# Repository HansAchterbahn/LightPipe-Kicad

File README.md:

# LightPipe - Main PCB (Kicad)

LightPipes are colorful lighting pipes that can be combined to create complex and interesting geometries. The LightPipe project is based on the easily addressable APA102 RGB LEDs. Each LED in a LightPipe geometry can be addressed individually.

The LightPipe project uses the PCB in this project in a slightly modified form as input and output PCB. On the input side, it simply accepts data from a 3.5 jack and power from an XT30 connector. On the output side, the data is output to the next LightPipe via the same jack and power is supplied via the same XT30 connector.

An additional 3.5 female connector is used to tunnel the data from the output PCB back to the input PCB. With this arrangement it is possible to realize a complete tree structure and therefore to create arbitrary geometries.

In this repository you will find the schematics and board layouts created in KiCad. You will also find a 3D model of the PCB.

*Fork me and have fun!*

**LightPipe - First Prototyep @ Neotopia Hackspace in Göttingen**

## PCB 3D view

Animated 3D STL model: [kibot/3d/model](kibot/3d/model)

__Top view__

__Bottom view__

## Schematic

## Board

__Top view__

__Bottom view__

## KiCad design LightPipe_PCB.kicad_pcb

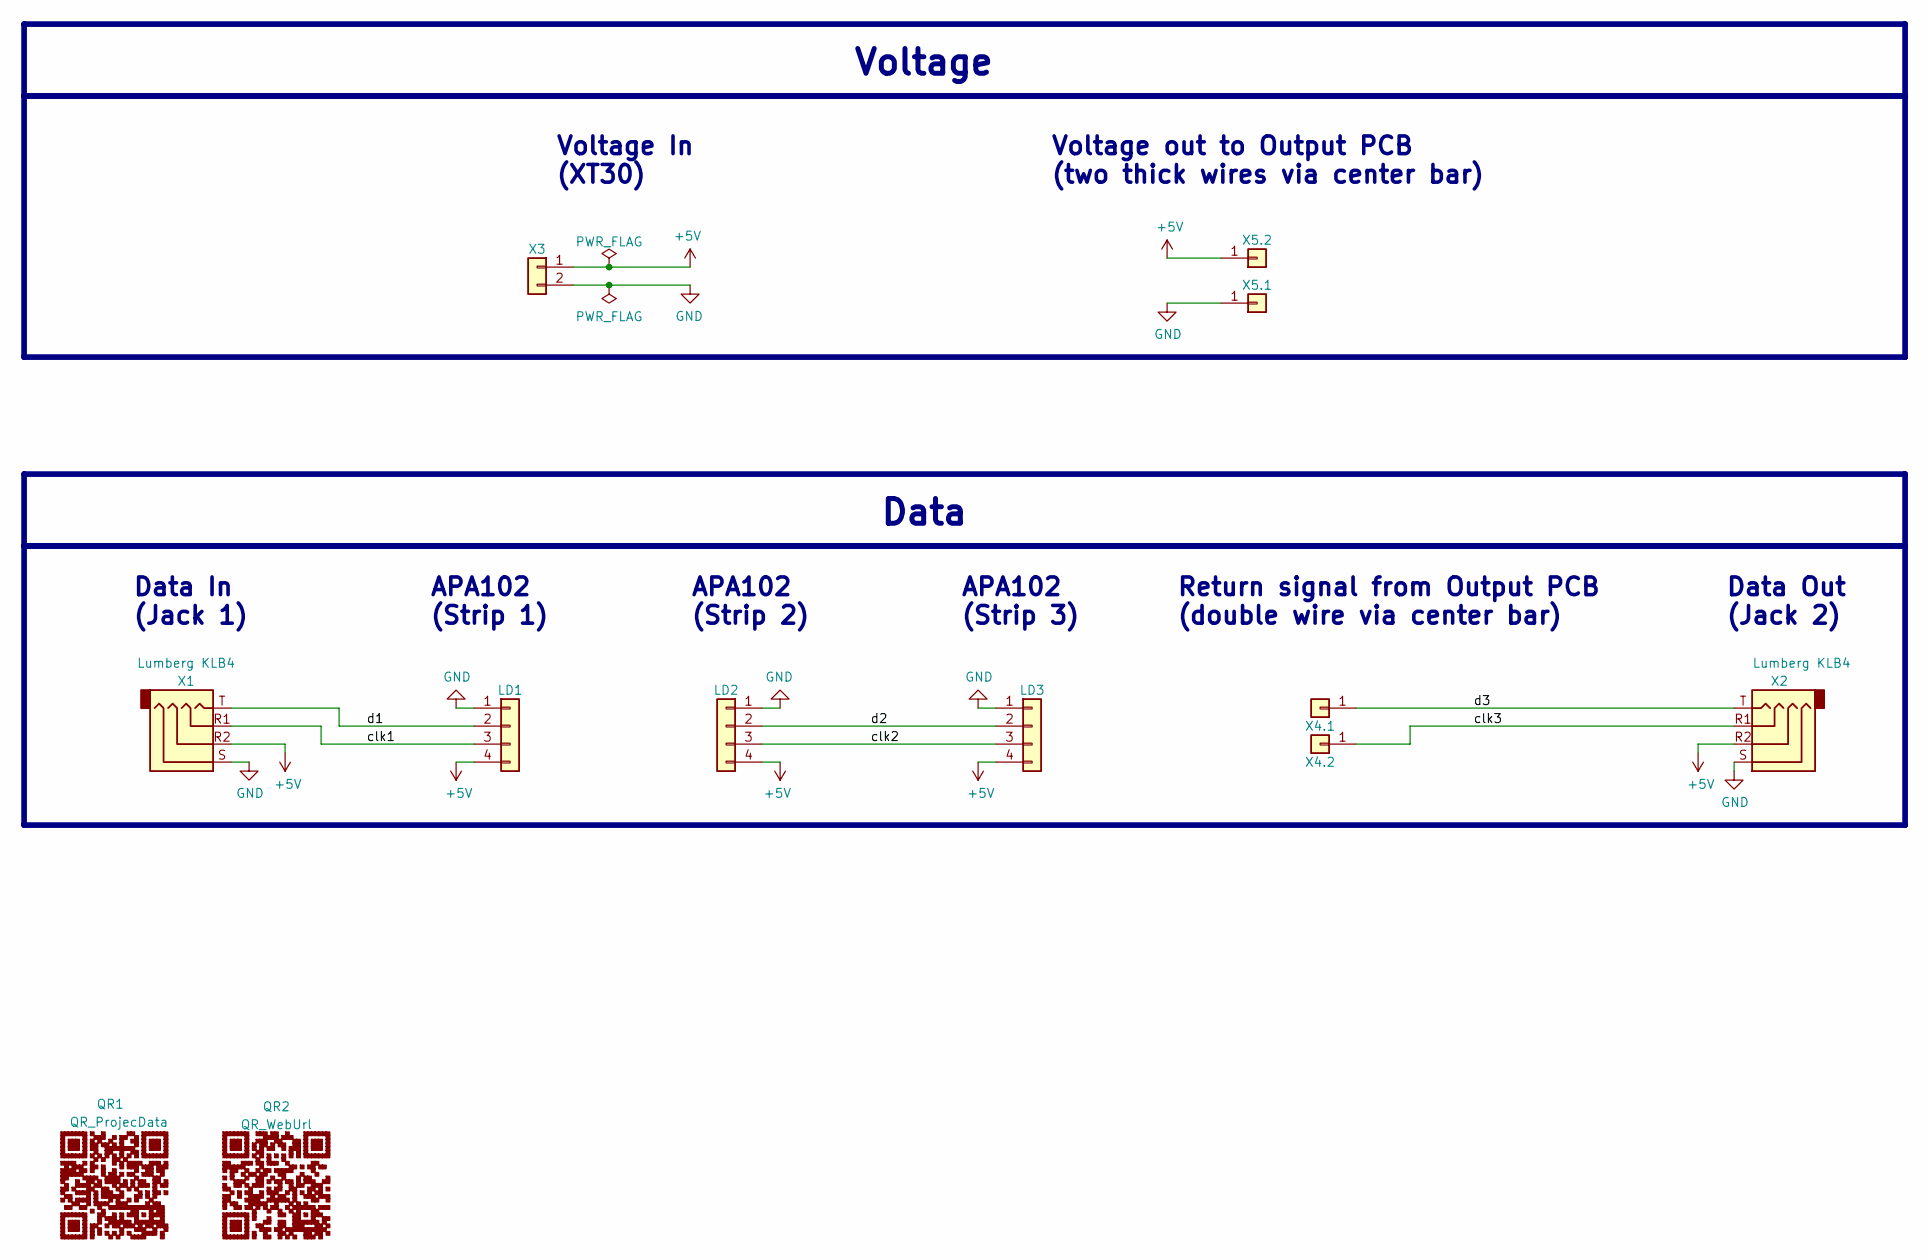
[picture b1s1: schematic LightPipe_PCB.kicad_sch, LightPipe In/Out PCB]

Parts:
LD1, LD3: APA102; APA102-Strip-Output
LD2: APA102; APA102-Strip-Input
QR1: QR_ProjecData
QR2: QR_WebUrl
X1, X2: Lumberg KLB4; Lumberg-KLB-4-Jack-3_5-180deg-turnable
X3: XT30; LCSC# C108769
X4.1, X4.2: Cable-0.7mm; Solder-Pad-THT-0.7mm
X5.1, X5.2: Cable-1.5mm; Solder-Pad-THT-1.5mm

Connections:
+5V: LD1.4, LD2.4, LD3.4, X1.R2, X2.R2, X3.1, X5.2.1
/clk1: LD1.3, X1.R1
/clk2: LD2.3, LD3.3
/clk3: X2.R1, X4.2.1
/d1: LD1.2, X1.T
/d2: LD2.2, LD3.2
/d3: X2.T, X4.1.1
GND: LD1.1, LD2.1, LD3.1, X1.S, X2.S, X3.2, X5.1.1

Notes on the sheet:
Data Out (Jack 2)
APA102 (Strip 1)
APA102 (Strip 3)
Data
Return signal from Output PCB (double wire via center bar)
Data In (Jack 1)
APA102 (Strip 2)
Voltage out to Output PCB (two thick wires via center bar)
Voltage
Voltage In (XT30)

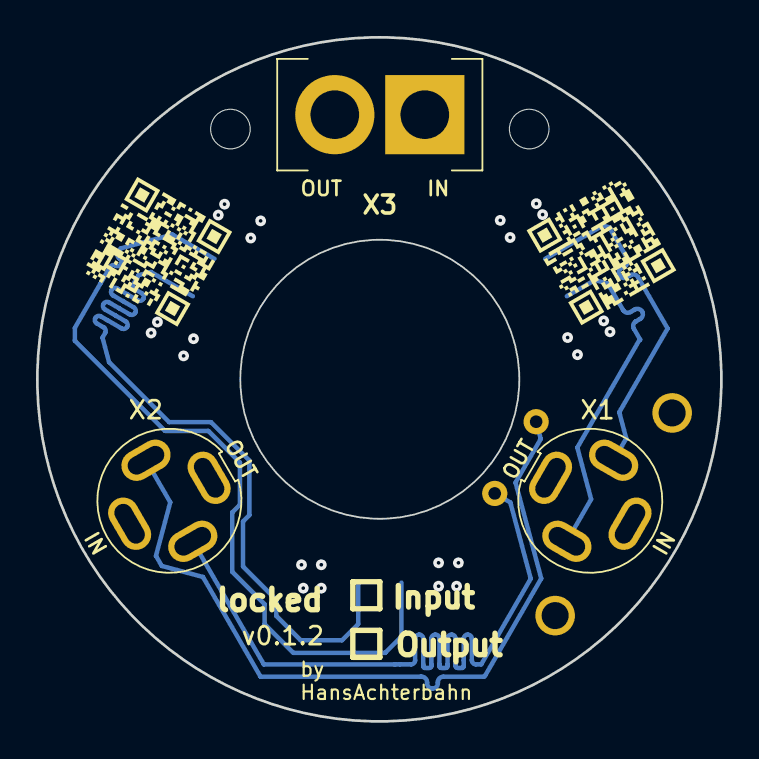
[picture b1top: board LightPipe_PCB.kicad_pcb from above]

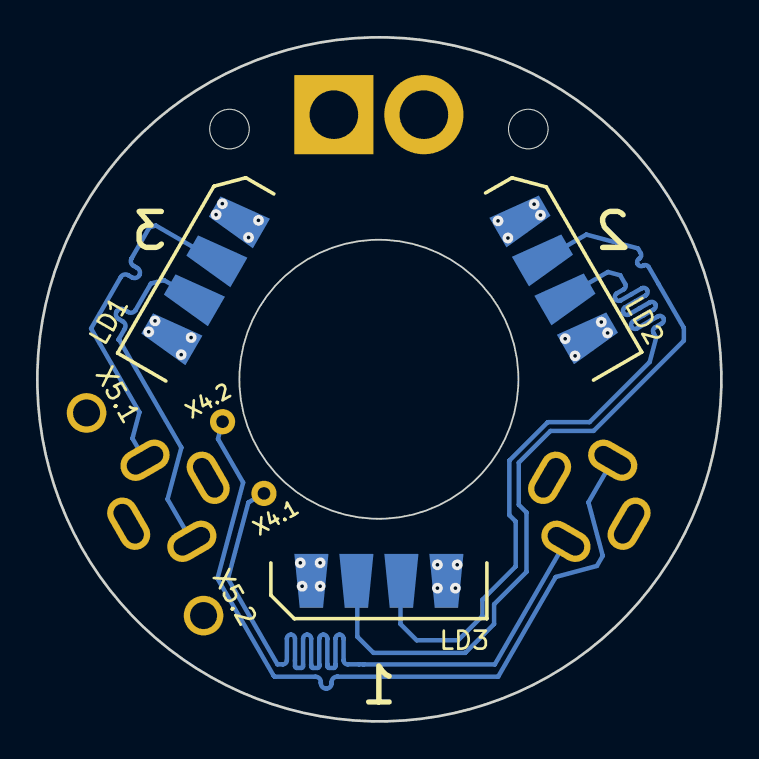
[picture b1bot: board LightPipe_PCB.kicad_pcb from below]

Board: 4 copper layers, 38.0 x 38.0 mm, 14 parts (7 on the bottom side), 8 nets.

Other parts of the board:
M1, M2: 2.2mm_M2; MountingHole_2.2mm_M2

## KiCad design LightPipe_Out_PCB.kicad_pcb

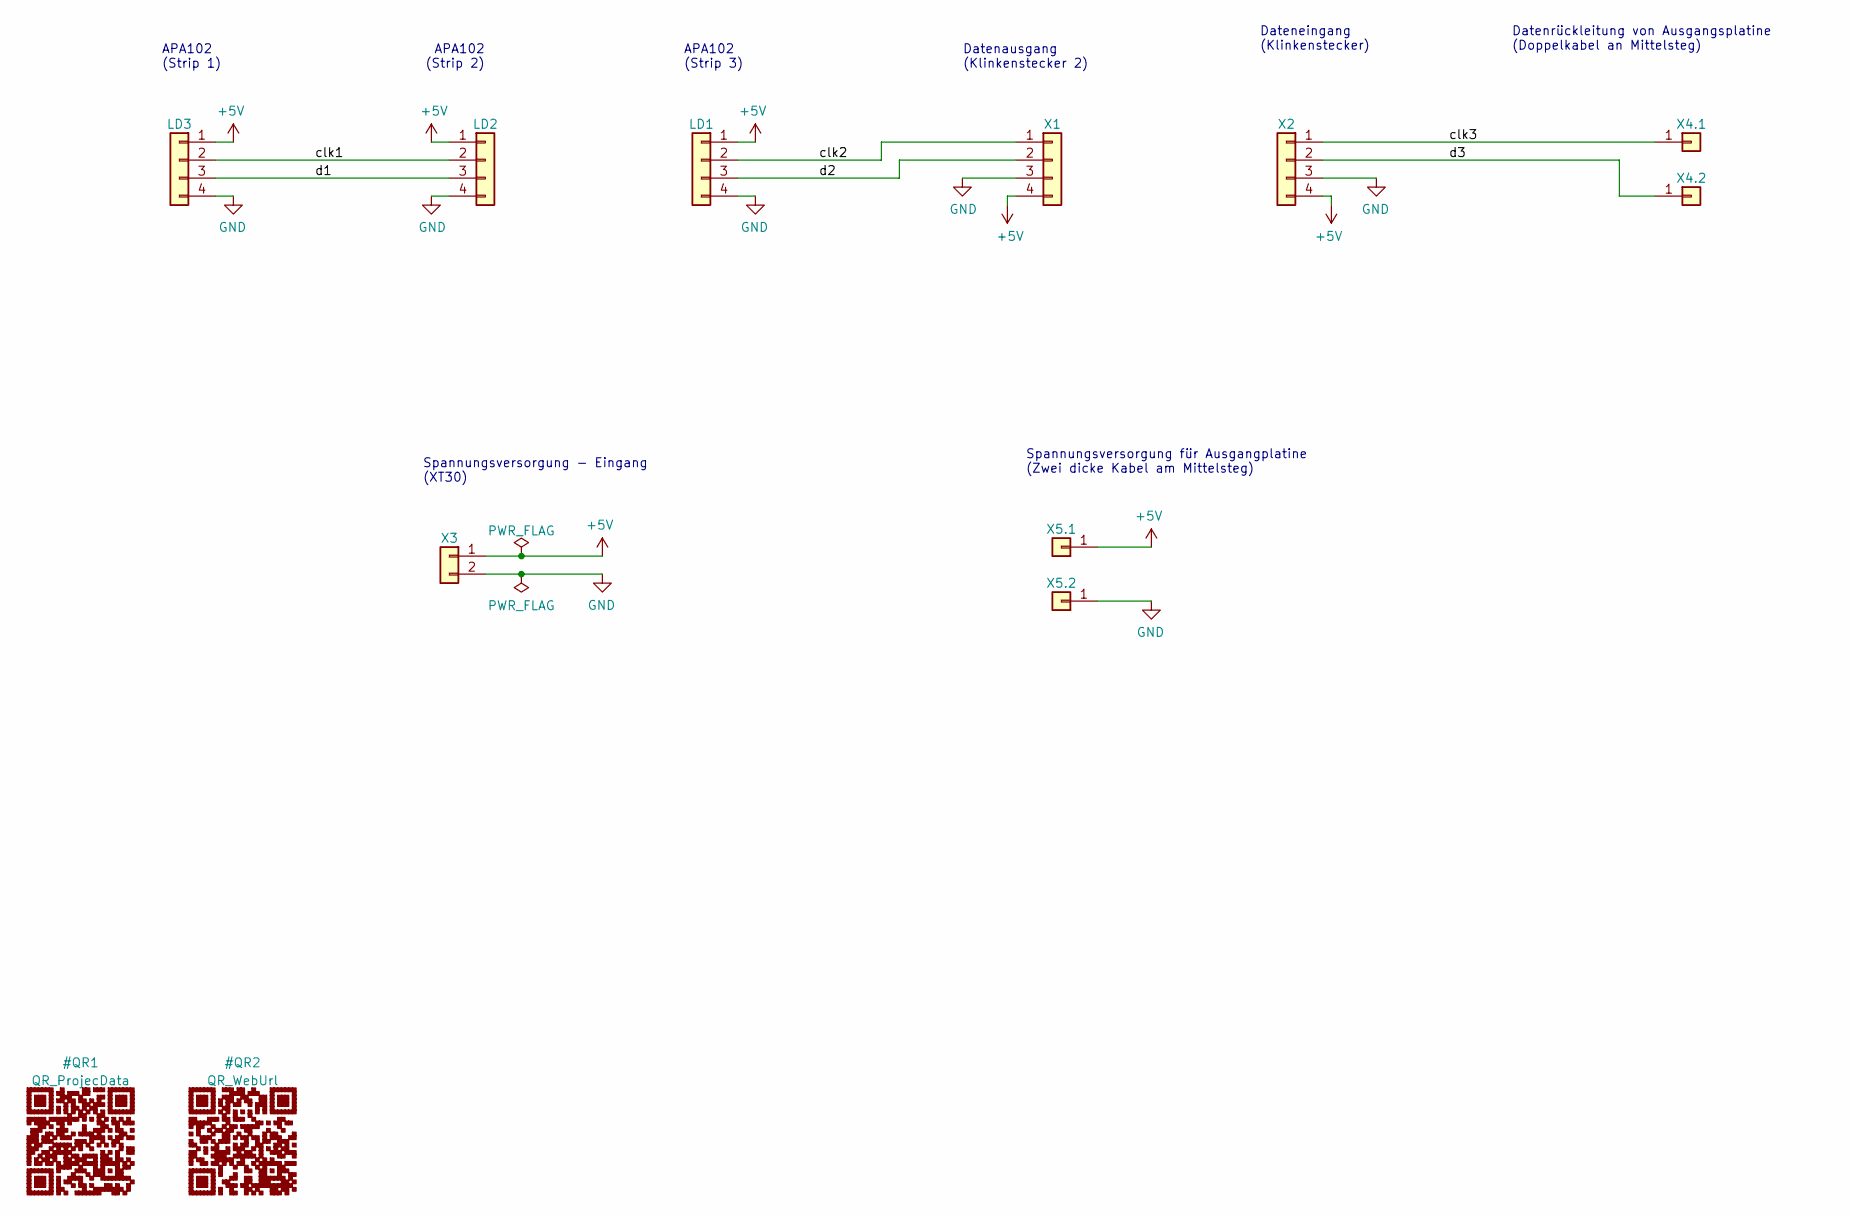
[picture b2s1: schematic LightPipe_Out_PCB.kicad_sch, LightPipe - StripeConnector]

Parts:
LD1, LD3: Conn_01x04; APA102-Strip-Output
LD2: Conn_01x04; APA102-Strip-Input
X1, X2: Conn_01x04; Lumberg-KLB-4-Klinkensteckverbinder-3_5-180deg-turnable
X3: Conn_01x02; XT30
X4.1, X4.2: Conn_01x01; Solder-Pad-THT-0.7mm
X5.1, X5.2: Conn_01x01; Solder-Pad-THT-1.5mm

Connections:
+5V: LD1.1, LD2.1, LD3.1, X1.4, X2.4, X3.1, X5.1.1
/clk1: LD2.2, LD3.2
/clk2: LD1.2, X1.1
/clk3: X2.1, X4.1.1
/d1: LD2.3, LD3.3
/d2: LD1.3, X1.2
/d3: X2.2, X4.2.1
GND: LD1.4, LD2.4, LD3.4, X1.3, X2.3, X3.2, X5.2.1

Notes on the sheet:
Dateneingang (Klinkenstecker)
APA102 (Strip 3)
APA102 (Strip 1)
Datenrückleitung von Ausgangsplatine (Doppelkabel an Mittelsteg)
Datenausgang (Klinkenstecker 2)
APA102 (Strip 2)
Spannungsversorgung für Ausgangplatine (Zwei dicke Kabel am Mittelsteg)
Spannungsversorgung - Eingang (XT30)

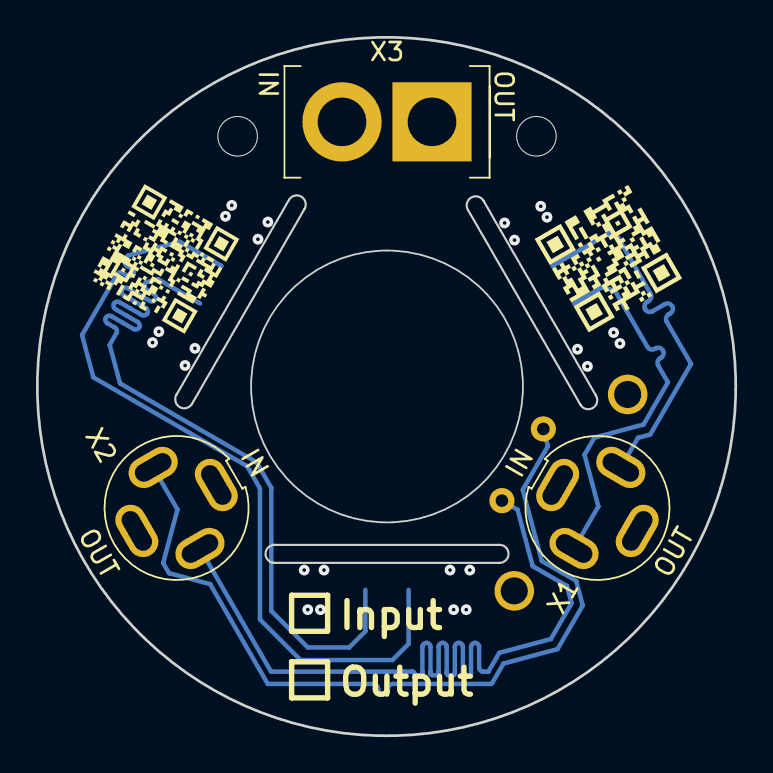
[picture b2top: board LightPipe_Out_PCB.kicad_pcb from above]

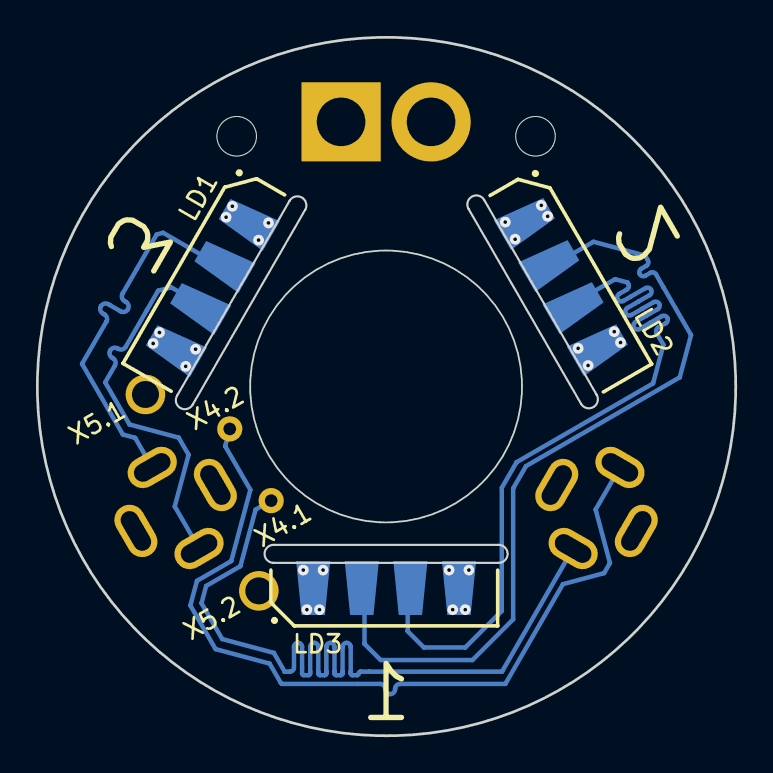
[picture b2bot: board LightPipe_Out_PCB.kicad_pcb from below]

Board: 4 copper layers, 38.8 x 38.8 mm, 13 parts (7 on the bottom side), 8 nets.

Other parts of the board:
M1: MountingHole_2.2mm_M2
QR1: QR_ProjecData
QR2: QR_WebUrl

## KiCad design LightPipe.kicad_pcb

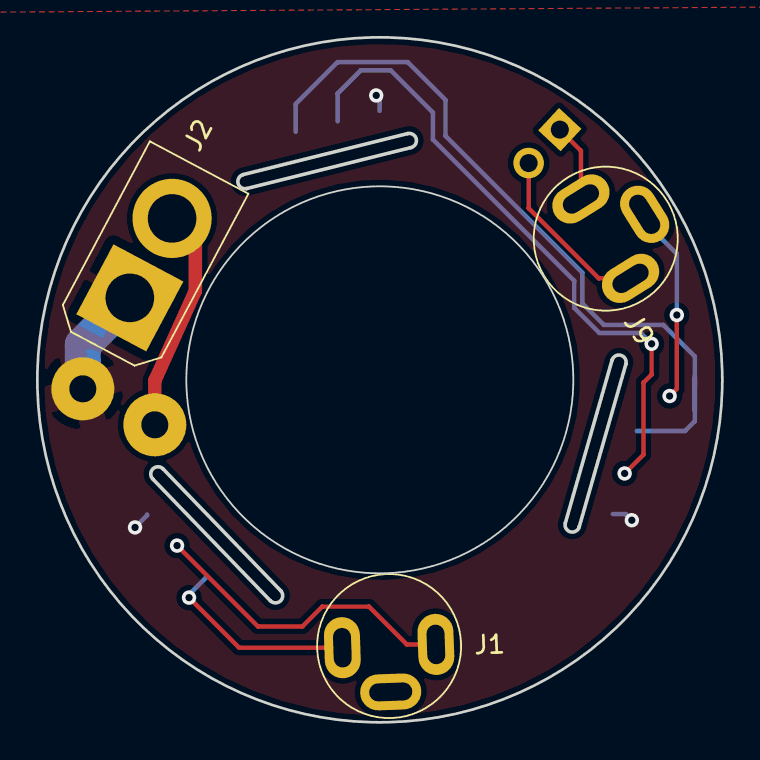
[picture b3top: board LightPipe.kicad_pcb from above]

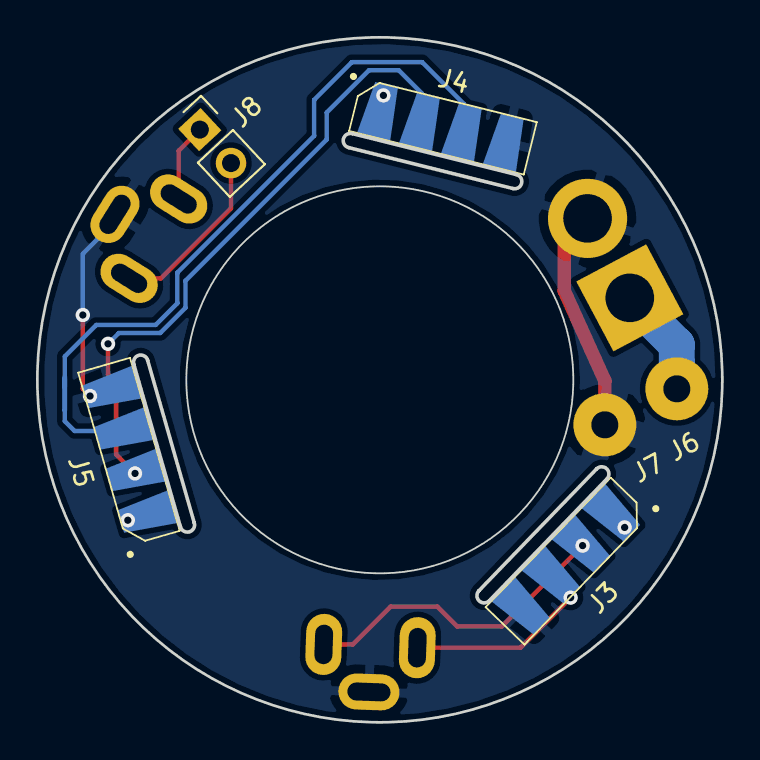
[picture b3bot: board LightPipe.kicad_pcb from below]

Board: 2 copper layers, 38.1 x 38.1 mm, 9 parts (6 on the bottom side), 8 nets.

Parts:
J1, J9: Conn_01x03; Lumberg-KLB-4-Klinkensteckverbinder-3_5
J2: Conn_01x02; XT30
J3, J4, J5: Conn_01x04; APA102-through
J6, J7: Conn_01x01; SolderWire-0.15sqmm_1x01_D0.5mm_OD1.5mm
J8: Conn_01x02; PinSocket_1x02_P2.54mm_Vertical

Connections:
+5V: J2.1, J3.1, J4.1, J5.1, J6.1
GND: J1.3, J2.2, J3.4, J4.4, J5.4, J7.1, J9.3
clk1: J1.1, J3.2
clk2: J4.2, J5.2
clk3: J8.1, J9.1
d1: J1.2, J3.3
d2: J4.3, J5.3
d3: J8.2, J9.2

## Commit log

2020-10-24 First schematic draft
2021-08-06 first PCB draft
2023-01-01 PCB looks quite good
2023-01-01 changed position of some silkscreen names
2023-01-12 [PCB] New Design features to use the PCB as In- and Out-PCB
2023-01-16 Changed designators from J? to X? and LD? | Improved Footprints
2023-01-28 [PCB] Improved footprints | optimized footprint locations | optimized wires
2023-01-28 [clean] removed old schematic file type
2023-01-28 [doc] Create KiBot export and a basic documentation in README.md
2023-01-28 [clean] Removed old export folder
2023-01-28 [QR] Added QR-Code to schematic | defined QR-Code on Board to be not on schematic
2023-04-07 [pcb] Optimized X1 and X2 positon
2023-04-07 [clean] Renamed project to have a generic name for input and output pcb
2023-04-07 [clean] Optimized schematic to be easy readable as input PCB | changed 3D bodys in PCB to Input PCB positions | update date, company, project name and QR-code in schematic and board
2023-04-10 [mechanical constrains] increased inner board diameter | reduced outer board diameter | added PCB name, version and creator to silkscreen
2023-04-10 [kibot] Executed Kibot script to generate documentation, manufacturing and assembly data
2023-04-12 [DRC] Solved DRC errors
2023-04-12 [kibot] Improved Settings: Inner layer in Gerber export were missing | reduced image size of 3d rendered PCB
2023-04-28 [clean] improved schematic and pcb to be easier to read in Input-Mode
2023-05-04 [clean] improved schematic and pcb to be easier to read in Input-Mode 2
2023-05-06 [PCB] Update footprint APA102 → Reduced the size of the slit in the PCB
2023-05-21 [PCB] Fixed Fab layers | added attributes to components
2023-05-21 [Kibot] Splited basic-export in to basic-export and 3d-export → better performance for basic-export
2023-05-21 [Kibot] Run job 'basic-export' and '3d-export'
2023-10-18 [WIP] Optimize PCB for more common LED-Strip (GND, D, CLK, 5V)
2023-10-18 Optimize PCB for more common LED-Strip (GND, D, CLK, 5V) → It could be a good idea to change X4.1, X4.2, X5.1 and X5.2 to a standard footprint. There is always trouble with this custom footprints.
2023-10-19 Try to run KiBot - but it does not work well with KiCad 7.0 → Downgrade to KiCad 6.0?
2023-10-26 Optimized schematic and PCB by checking Gerber Data
2023-10-26 Optimized KiBot script to make it work as good as possible with KiCad 7.0
2023-10-30 [PCB] Changed Layer In1 with In2 + Kibot Export
